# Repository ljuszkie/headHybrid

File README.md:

# headHybrid 
Simple hybrid headphone amplifier. Project was created in
KiCad BZR 5054 on Linux, verified to be editable in KiCad 4.0.2, which
is target version (switch to new version soon). Board view image and
pdf schematic can be found in preview folder.

Prosty hybrydowy wzmacniacz słuchawkowy. Projekt utworzony w KiCadzie
BZR 5054 na Linuksie, można go edytować w KiCadzie 4.0.2, który jest
docelową wersją (przejście na nową wersję wkrótce). Obrazek
z widokiem płytki i schemat w formacie pdf znajdują się w folderze
preview.

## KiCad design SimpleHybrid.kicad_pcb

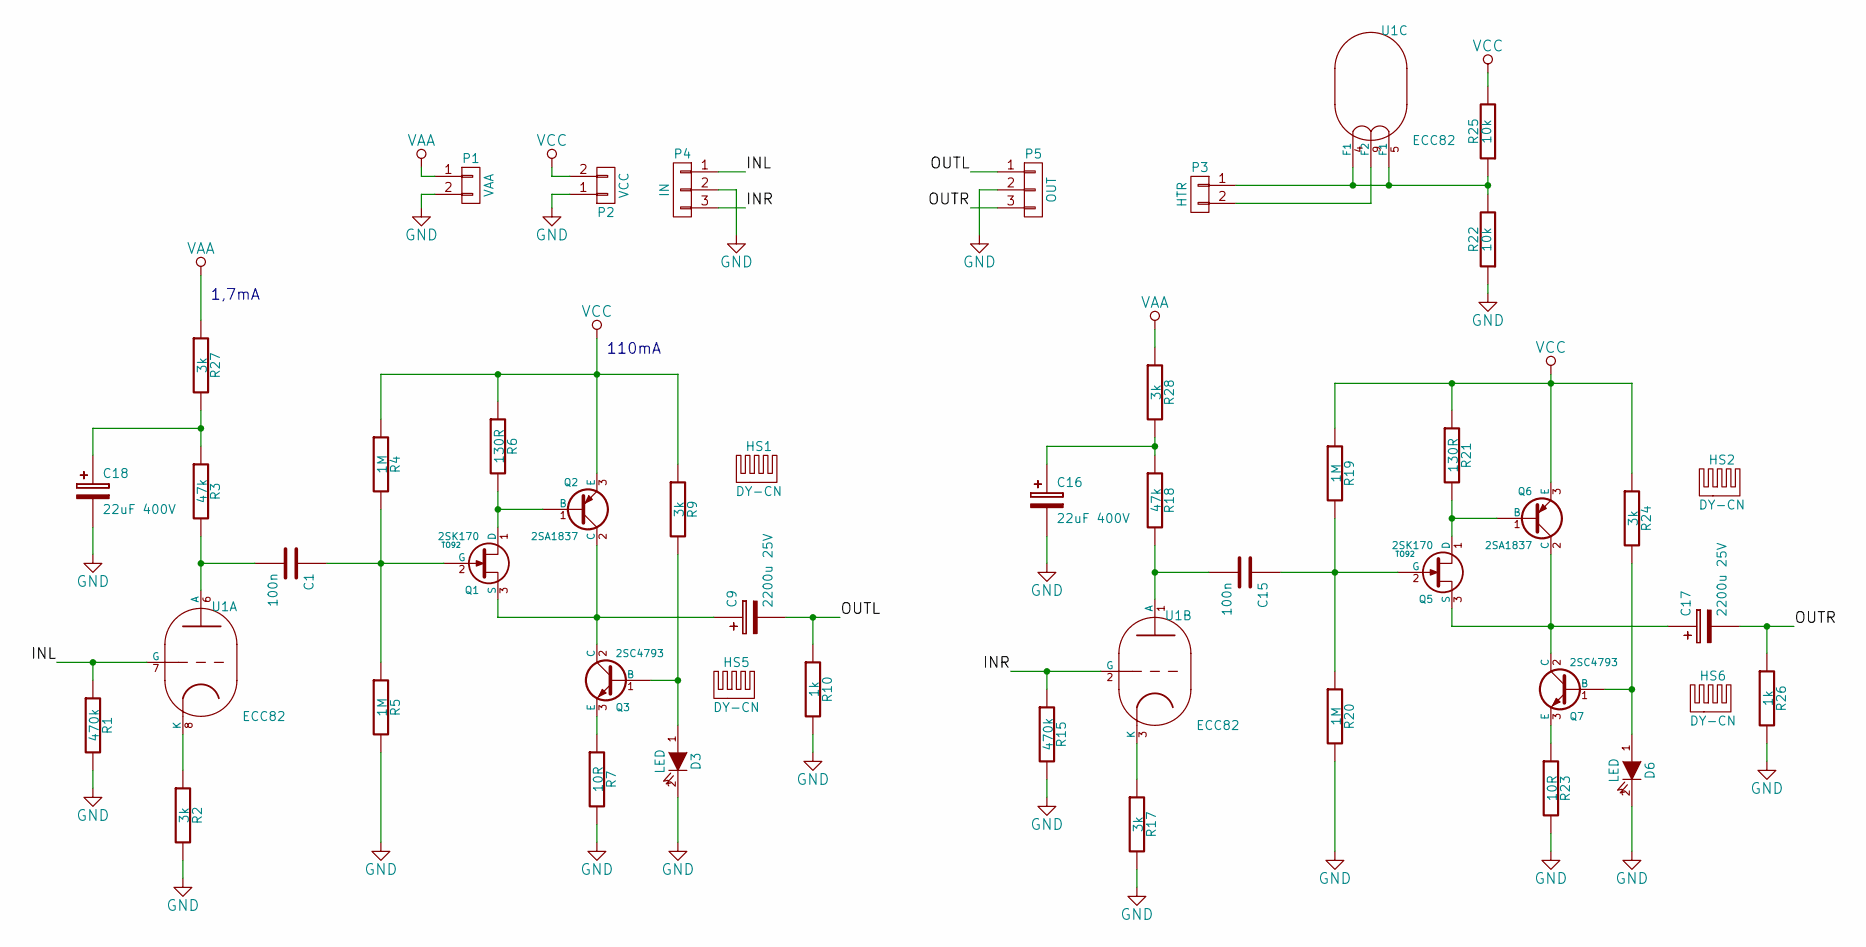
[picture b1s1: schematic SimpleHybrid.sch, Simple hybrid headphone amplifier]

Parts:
C1, C15: 100n
C9, C17: 2200u 25V
C16, C18: 22uF 400V
D3, D6: LED
HS1, HS2, HS5, HS6: DY-CN
P1: VAA
P2: VCC
P3: HTR
P4: IN
P5: OUT
Q1, Q5: 2SK170; TO92
Q2, Q6: 2SA1837
Q3, Q7: 2SC4793
R1, R15: 470k
R2, R9, R17, R24, R27, R28: 3k
R3, R18: 47k
R4, R5, R19, R20: 1M
R6, R21: 130R
R7, R23: 10R
R10, R26: 1k
R22, R25: 10k
U1: ECC82; VALVE-NOVAL_P

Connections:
/INL: P4.1, R1.1, U1.7 (G)
/INR: P4.3, R15.1, U1.2 (G)
/OUTL: C9.2, P5.1, R10.1
/OUTR: C17.2, P5.3, R26.1
GND: C16.2, C18.2, D3.2 (K), D6.2 (K), P1.2, P2.1, P4.2, P5.2, R1.2, R2.2, R5.2, R7.2, R10.2, R15.2, R17.2, R20.2, R22.1, R23.2, R26.2
unnamed: C1.1, Q1.2 (G), R4.2, R5.1
unnamed: C1.2, R3.2, U1.6 (A)
unnamed: C9.1, Q1.3 (S), Q2.2 (C), Q3.2 (C)
unnamed: C15.1, Q5.2 (G), R19.2, R20.1
unnamed: C15.2, R18.2, U1.1 (A)
unnamed: C16.1, R18.1, R28.2
unnamed: C17.1, Q5.3 (S), Q6.2 (C), Q7.2 (C)
unnamed: C18.1, R3.1, R27.2
unnamed: D3.1 (A), Q3.1 (B), R9.2
unnamed: D6.1 (A), Q7.1 (B), R24.2
unnamed: P3.1, R22.2, R25.1, U1.4 (F1), U1.5 (F1)
unnamed: P3.2, U1.9 (F2)
unnamed: Q1.1 (D), Q2.1 (B), R6.2
unnamed: Q3.3 (E), R7.1
unnamed: Q5.1 (D), Q6.1 (B), R21.2
unnamed: Q7.3 (E), R23.1
unnamed: R2.1, U1.8 (K)
unnamed: R17.1, U1.3 (K)
VAA: P1.1, R27.1, R28.1
VCC: P2.2, Q2.3 (E), Q6.3 (E), R4.1, R6.1, R9.1, R19.1, R21.1, R24.1, R25.2

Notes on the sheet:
1,7mA
110mA

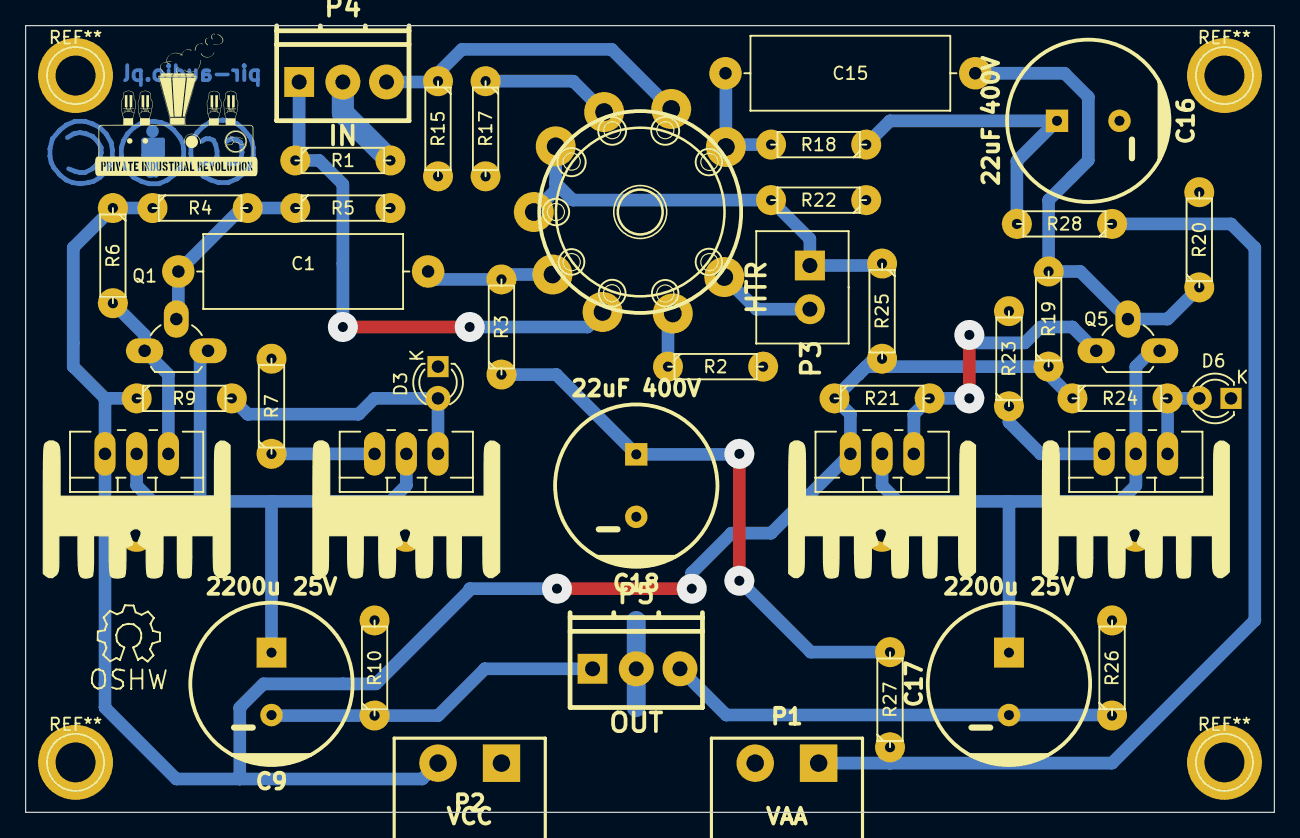
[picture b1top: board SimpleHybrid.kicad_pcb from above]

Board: 2 copper layers, 100.0 x 63.0 mm, 46 parts (0 on the bottom side), 25 nets.

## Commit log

2016-08-23 Added project files
2016-09-11 README corrections
2016-09-11 README updated and LICENSE added Preview added

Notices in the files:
SimpleHybrid.kicad_pcb:
licensed under CC BY SA 4.0 International
SimpleHybrid.sch:
https://creativecommons.org/licenses/by-sa/4.0
